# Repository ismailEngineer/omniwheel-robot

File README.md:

# omniwheel-robot
This repository contains all files for a 3 omniwheel robot, a small protoype to educate the control system

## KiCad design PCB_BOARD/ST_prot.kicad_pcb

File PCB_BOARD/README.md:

# PCB_BOARD
this repository contain all electronics shematics and PCB routing in Kicad

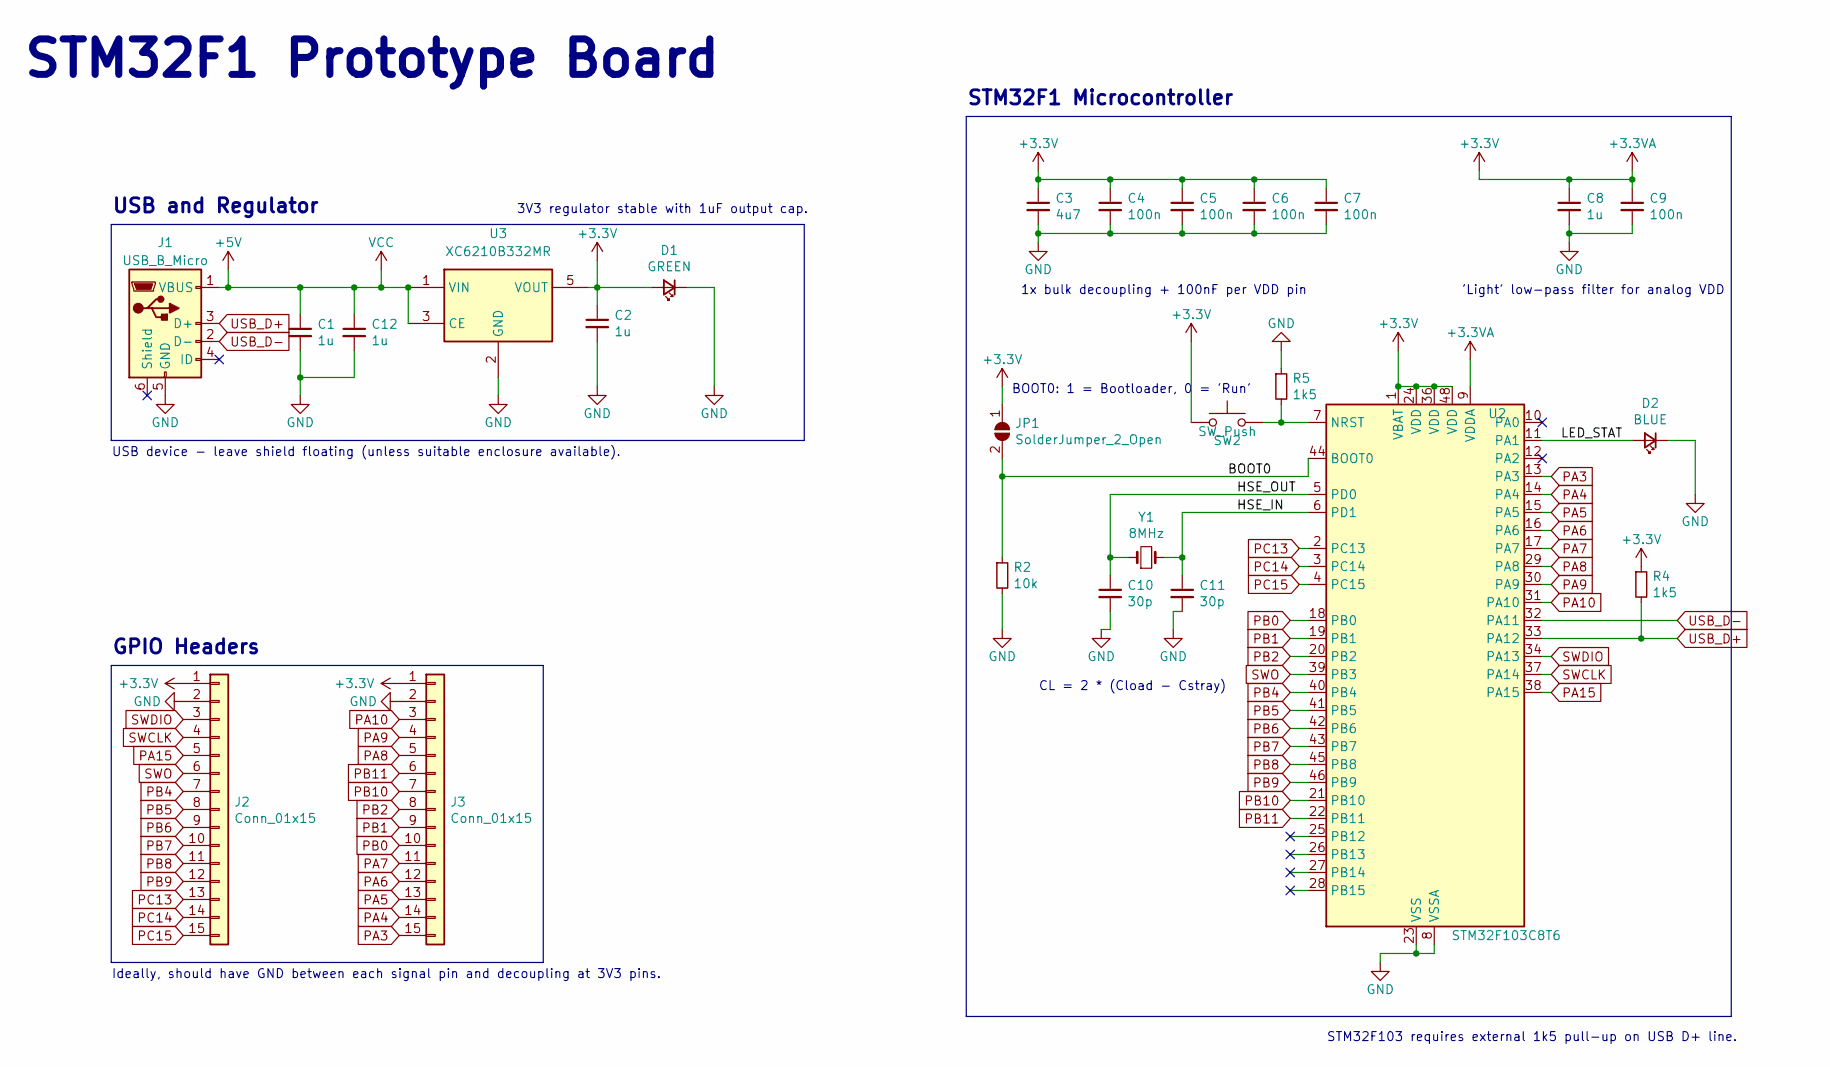
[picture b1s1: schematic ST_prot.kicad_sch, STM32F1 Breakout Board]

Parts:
C1: 1u; C_0603_1608Metric_Pad1.08x0.95mm_HandSolder; LCSC Part # C15849
C2, C12: 1u; C_0603_1608Metric; LCSC Part # C15849
C3: 4u7; C_0603_1608Metric; LCSC Part # C19666
C4, C5, C6, C7, C9: 100n; C_0603_1608Metric; LCSC Part # C1525
C8: 1u; C_0603_1608Metric; LCSC Part # C52923
C10, C11: 30p; C_0603_1608Metric; LCSC Part # C1570
D1: GREEN; LED_0603_1608Metric; LCSC Part # C72043
D2: BLUE; LED_0603_1608Metric; LCSC Part # C72041
J1: USB_B_Micro; USB_Micro-B_Wuerth_629105150521
J2, J3: Conn_01x15; PinHeader_1x15_P2.54mm_Vertical
JP1: SolderJumper_2_Open; SolderJumper-2_P1.3mm_Open_Pad1.0x1.5mm
R2: 10k; R_0402_1005Metric; LCSC Part # C25744
R4, R5: 1k5; R_0603_1608Metric; LCSC Part # C25867
SW2: SW_Push; SW_SPST_CK_RS282G05A3
U2: STM32F103C8T6; LQFP-48_7x7mm_P0.5mm; LCSC Part # C8734
U3: XC6210B332MR; SOT-23-5
Y1: 8MHz; Crystal_SMD_HC49-SD; LCSC Part # C115962

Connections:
+3.3V: C2.1, C3.1, C4.1, C5.1, C6.1, C7.1, C8.1, C9.1, D1.2 (A), J2.1, J3.1, JP1.1 (A), R4.1, SW2.1, U2.1 (VBAT), U2.9 (VDDA), U2.24 (VDD), U2.36 (VDD), U2.48 (VDD), U3.5 (VOUT)
+5V: C1.1, C12.1, J1.1 (VBUS), U3.1 (VIN), U3.3 (CE)
/BOOT0: JP1.2 (B), R2.1, U2.44 (BOOT0)
/HSE_IN: C11.1, U2.6 (PD1), Y1.2
/HSE_OUT: C10.1, U2.5 (PD0), Y1.1
/LED_STAT: D2.2 (A), U2.11 (PA1)
GND: C1.2, C2.2, C3.2, C4.2, C5.2, C6.2, C7.2, C8.2, C9.2, C10.2, C11.2, C12.2, D1.1 (K), D2.1 (K), J1.5 (GND), J2.2, J3.2, R2.2, R5.1, U2.8 (VSSA), U2.23 (VSS), U2.35 (VSS), U2.47 (VSS), U3.2 (GND)
unnamed: R5.2, SW2.2, U2.7 (NRST)
PA3: J3.15, U2.13 (PA3)
PA4: J3.14, U2.14 (PA4)
PA5: J3.13, U2.15 (PA5)
PA6: J3.12, U2.16 (PA6)
PA7: J3.11, U2.17 (PA7)
PA8: J3.5, U2.29 (PA8)
PA9: J3.4, U2.30 (PA9)
PA10: J3.3, U2.31 (PA10)
PA15: J2.5, U2.38 (PA15)
PB0: J3.10, U2.18 (PB0)
PB1: J3.9, U2.19 (PB1)
PB2: J3.8, U2.20 (PB2)
PB4: J2.7, U2.40 (PB4)
PB5: J2.8, U2.41 (PB5)
PB6: J2.9, U2.42 (PB6)
PB7: J2.10, U2.43 (PB7)
PB8: J2.11, U2.45 (PB8)
PB9: J2.12, U2.46 (PB9)
PB10: J3.7, U2.21 (PB10)
PB11: J3.6, U2.22 (PB11)
PC13: J2.13, U2.2 (PC13)
PC14: J2.14, U2.3 (PC14)
PC15: J2.15, U2.4 (PC15)
SWCLK: J2.4, U2.37 (PA14)
SWDIO: J2.3, U2.34 (PA13)
SWO: J2.6, U2.39 (PB3)
USB_D+: J1.3 (D+), R4.2, U2.33 (PA12)
USB_D-: J1.2 (D-), U2.32 (PA11)

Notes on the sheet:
STM32F103 requires external 1k5 pull-up on USB D+ line.
1x bulk decoupling + 100nF per VDD pin
3V3 regulator stable with 1uF output cap.
Ideally, should have GND between each signal pin and decoupling at 3V3 pins.
USB and Regulator
BOOT0: 1 = Bootloader, 0 = 'Run'
'Light' low-pass filter for analog VDD
GPIO Headers
STM32F1 Prototype Board
USB device - leave shield floating (unless suitable enclosure available).
CL = 2 * (Cload - Cstray)
STM32F1 Microcontroller

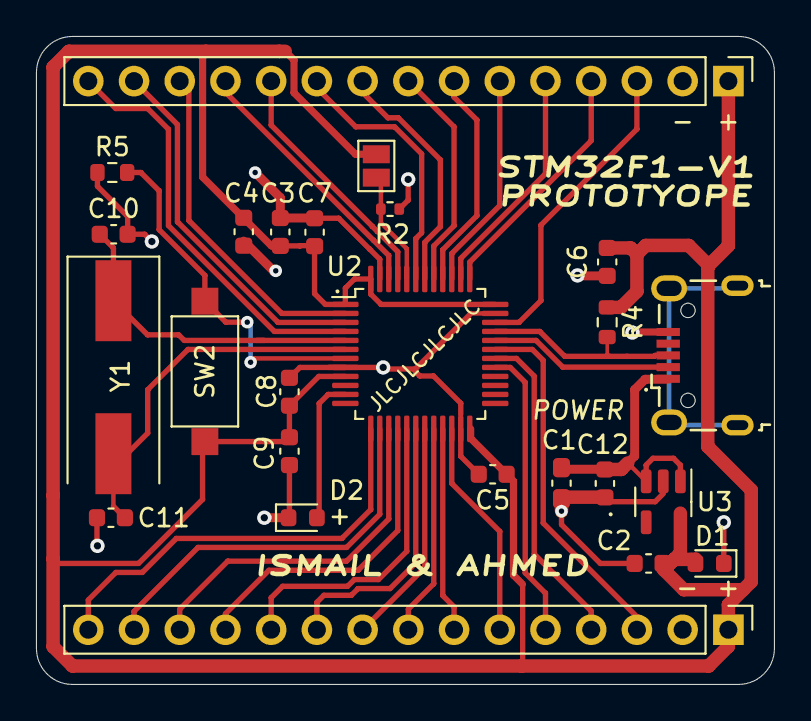
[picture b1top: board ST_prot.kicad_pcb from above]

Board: 2 copper layers, 41.0 x 36.0 mm, 25 parts (0 on the bottom side), 36 nets.

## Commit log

2023-11-15 Init commit
2023-11-16 refactor 3D base
2023-11-16 Add later cover to robot assembly
2023-11-17 reorder files
2023-11-20 restructer repoé
2023-11-20 repalce Readme file
2023-11-20 Create ROS package for controller
2023-11-30 Initial commit of electonic sch a,d pcb
2023-12-01 Edit footprint and reroute pcb
2023-12-02 Finish prototype v1 PCB
2023-12-04 Add new navigation package with camera configuration and laser scan
2023-12-04 ignore backups pcb files and vscode local file config
2023-12-04 Add robot simulation package
2023-12-04 ignore vscode confi for robot simulation package
2023-12-04 Add urdf models and meshes
2023-12-04 Add READMEs for all packages
2023-12-04 Add Readmes for elecronics and mechanical design
2024-02-02 Add zmq-node communication
2024-02-02 Json message via zmq
2024-02-02 Build custom JSON message for robot
2024-02-02 fix erreur / in ip adress
2024-02-02 Change json message
2024-02-02 Build first qt windows
2024-02-03 Connect qt windows with raspberry via zmq
2024-02-05 Improve gui interfaces (Add icon and organize)
2024-02-05 ignore pycache
2024-02-11 add dynamics to button and input boxes
2024-07-28 add main proto pcb
2024-07-28 Add basic web dashboard for commands
2024-07-28 adjust js cache problem
2024-07-29 add 3D modification
2024-07-29 Add motor arduino controllers
2024-07-29 add i2c script communication between arduino uno and raspberry pi 3
2024-07-29 Connect button to motors control
2024-08-09 [NOT TESTED] general hardware controller script
2024-08-09 [NOT TESTED] arg sys and init app function
2024-08-10 adjust front end layout
2024-12-09 Adjust 3D design for PCB v1
2024-12-09 Update main PCB board with 3D step file
2024-12-10 Update PCB & Add bom with links to digikey
2024-12-15 Create 3D version of the proto
2024-12-16 Update 3D model PLA
2024-12-18 Final 3D design prototype v1
2024-12-18 Generate some gcodes for stl parts
2024-12-18 adjust driver etage 3d part
2024-12-18 Add buttons on off with 3d models
2024-12-18 Add missing hole to base 3D model
2024-12-19 Adjust main PCB proto v1 with the 3d model step and part in assembly robot
2024-12-20 Print L support for prototype
2024-12-23 Chnage web page design
2025-02-14 update pcb to origianl one
2025-02-15 Generate and save gerber files
2025-05-19 update pcb and 3d model of main board
2025-05-19 First script with all motors and encoders
2025-05-23 activate motors arduino
2025-05-26 add serial configuration
2025-05-26 send message serial when click buttons
2025-05-26 [debug] send message serial when click buttons
2025-05-29 [debug] edit control function
2025-05-29 [debug] adjust velocity
2025-05-29 [debug] add joystick control
2025-05-29 [debug] correct js joystick script
2025-05-30 [debug] bug recentring joystick
2025-07-27 Add PI controller for 1 motor
2025-08-01 Change motor sens and implement PID controller for all wheels
2025-08-01 Add documentation for kinematic model
2025-08-02 Adjust PI and add start caracter to send
2025-08-02 add plotter to visualize velocity graph for PI controller
2025-08-02 add serial comm for velocity between raspberry and arduino
2025-08-02 adjust PI controller
2025-08-03 add controller to controll manually like joystick
2025-08-03 increase velocity
2025-08-04 add velocity lecture in thread and tcp server to send velocity
2025-08-04 add tcp client to read velocity from server (raspberrypi)
2025-08-05 add omdometry estimation
2025-08-05 fix syntax error
2025-08-05 fix logic serial and tcp comm
2025-08-08 add ros nodes
2025-08-20 add utilitis scripts
